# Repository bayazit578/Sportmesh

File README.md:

# Sportmesh

## Описание проекта
Cистема КП для спортивного ориентирования, трейлов с возможностью мониторинга участников соревнований в реальном времени на основе кастомной mesh-сети

## Прошивка

Прошивка использует `Arduino`-фреймворк а преимущества лежащего под ней
фреймворка `esp-idf` (например задачи, очереди и семафоры из `FreeRTOS`)

### Зависимости

| Библиотека | Версия |
| --- | --- |
| [LoRaMesher][loramesher] | `1.0.0` |
| [RadioLib][radiolib] | `7.8.1` |
| [MFRC522][mfrc522] | `1.4.12` |
| [TM16xx LEDs and Buttons][tm16xx] | `0.7.2512` |

[loramesher]: https://github.com/LoRaMesher/LoRaMesher
[radiolib]: https://github.com/jgromes/RadioLib
[mfrc522]: https://github.com/miguelbalboa/rfid
[tm16xx]: https://github.com/maxint-rd/TM16xx

### Сборка

`debug`-конфигурация:
```shell
pio run -e debug
```

`release`-конфигурация:
```shell
pio run -e release
```

### Документация

Установите Doxygen и выполните:

```shell
doxygen Doxyfile
xdg-open docs/html/index.html
```

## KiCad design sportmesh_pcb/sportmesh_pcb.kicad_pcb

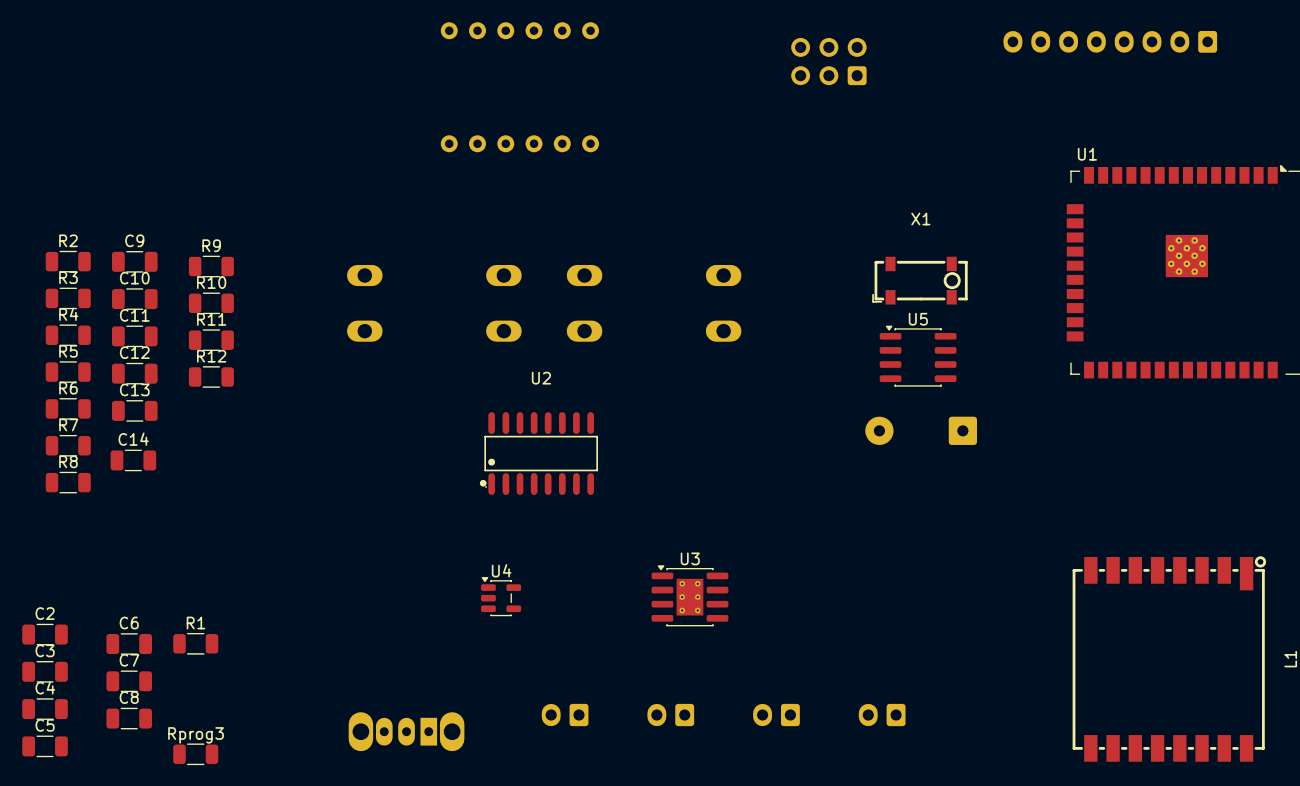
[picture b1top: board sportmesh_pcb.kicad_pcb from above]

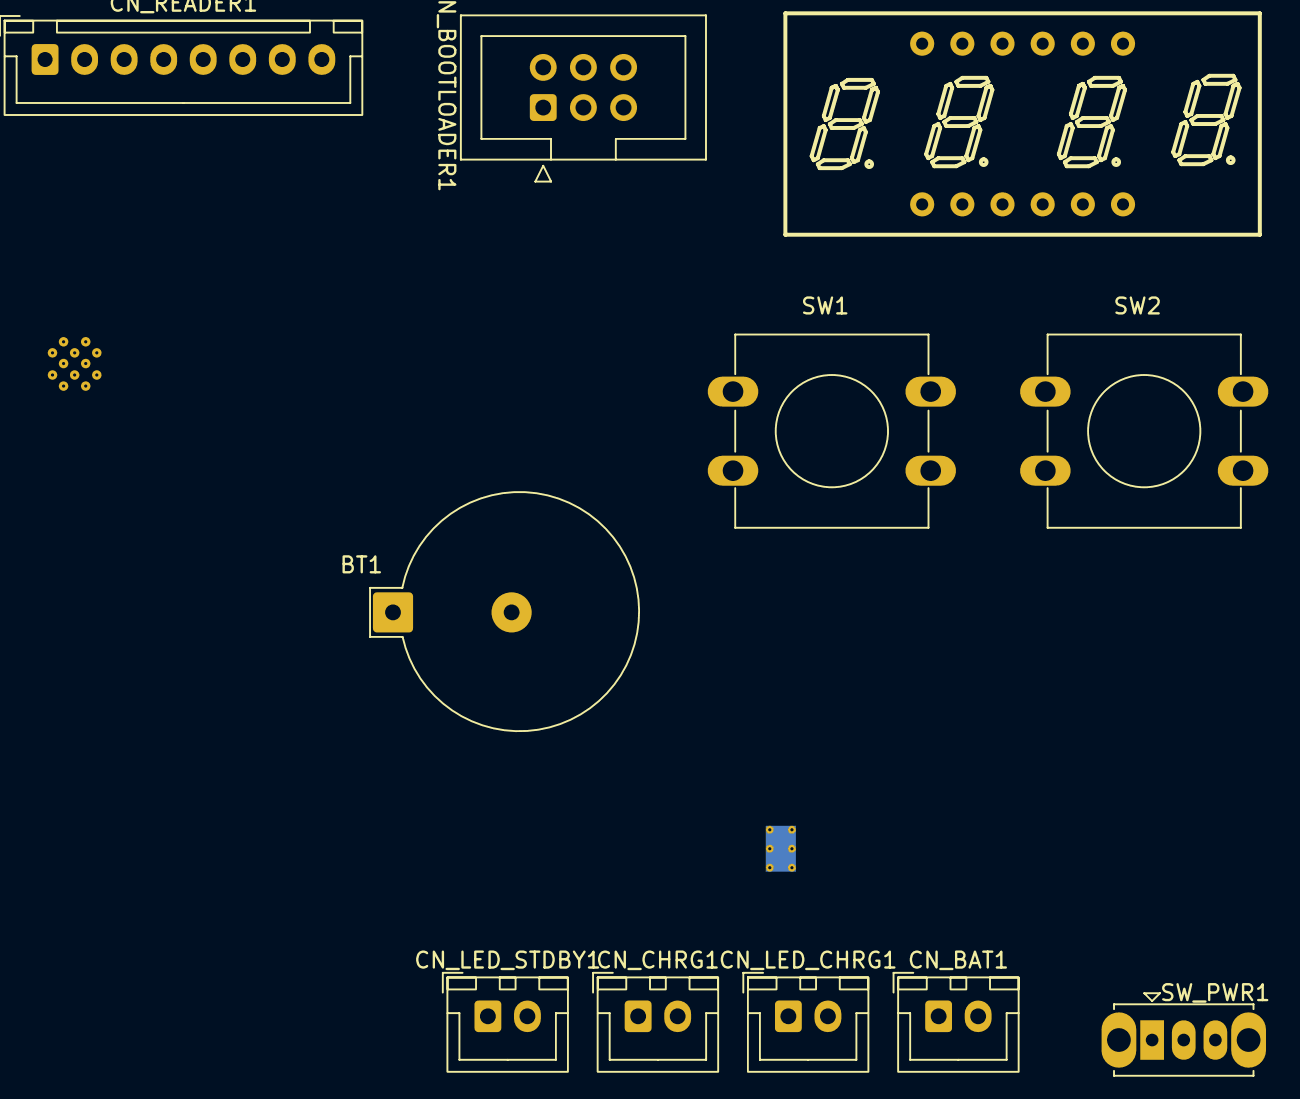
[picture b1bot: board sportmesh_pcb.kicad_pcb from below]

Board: 2 copper layers, 44 parts (11 on the bottom side), 45 nets, no tracks yet.

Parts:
BT1: Battery_Cell; BatteryHolder_KLS5-CR1220-01
C2, C4, C6: 10uF; C_1206_3216Metric
C3, C5, C10, C11: 0.1uF; C_1206_3216Metric
C7, C8, C9, C12, C13: 1uF; C_1206_3216Metric
C14: 3.3uF; C_1206_3216Metric
CN_BAT1: Conn_01x02_Pin; JST_XH_B2B-XH-A_1x02_P2.50mm_Vertical
CN_BOOTLOADER1: Conn_02x03_Odd_Even; IDC-Header_2x03_P2.54mm_Vertical
CN_CHRG1: Conn_01x02_Pin; JST_XH_B2B-XH-A_1x02_P2.50mm_Vertical
CN_LED_CHRG1: Conn_01x02_Pin; JST_XH_B2B-XH-A_1x02_P2.50mm_Vertical
CN_LED_STDBY1: Conn_01x02_Pin; JST_XH_B2B-XH-A_1x02_P2.50mm_Vertical
CN_READER1: Conn_01x08_Socket; JST_XH_B8B-XH-A_1x08_P2.50mm_Vertical
L1: RA-01SH; WIRELM-SMD_RA-01SH
LED1: FJ3461AH; LED-SEG-TH_12P-L30.0-W14.0-P2.54-S10.16-BL
R1, R12: 1K; R_1206_3216Metric
R2, R3: 3.3K; R_1206_3216Metric
R4, R5, R6, R7, R8, R9, R10, R11: 10K; R_1206_3216Metric
Rprog3: 3.3K; R_1206_3216Metric
SW1, SW2: SW_SPST; SW_PUSH-12mm
SW_PWR1: SW_SPDT; SW_Slide_SPDT_Straight_CK_OS102011MS2Q
U1: ESP32-WROOM-32D
U2: TM1650_C18211636; SOIC-16_L9.9-W3.9-P1.27-LS6.0-BL
U3: TP4056-42-ESOP8; SOIC-8-1EP_3.9x4.9mm_P1.27mm_EP2.41x3.3mm_ThermalVias
U4: TLV75733PDBV; SOT-23-5
U5: PCF8523T; SOIC-8_3.9x4.9mm_P1.27mm
X1: 6LC32768F06UC; OSC-SMD_4P-L8.0-W3.2-BL

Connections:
+3V3: C2.1, C3.1, C4.1, C5.1, C8.1, CN_BOOTLOADER1.2, CN_READER1.8, L1.3 (3.3V), R4.1, R5.1, R6.1, R7.1, R8.1, R9.1, R10.1, R11.2, R12.1, U1.2 (VDD), U2.10 (VDD), U4.5 (OUT)
/sheet_1/IO_0: CN_BOOTLOADER1.6, U1.25 (IO0)
/sheet_1/IO_5: L1.15 (NSS), U1.29 (IO5)
/sheet_1/IO_16: L1.4 (RESET), U1.27 (IO16)
/sheet_1/IO_17: L1.10 (BUSY), U1.28 (IO17)
/sheet_1/IO_18: L1.12 (SCK), U1.30 (IO18)
/sheet_1/IO_19: L1.13 (MISO), U1.31 (IO19)
/sheet_1/IO_22: L1.6 (DIO1), U1.36 (IO22)
/sheet_1/IO_23: L1.14 (MOSI), U1.37 (IO23)
/sheet_1/IO_32: R10.2, U1.8 (IO32), U5.6 (SCL)
/sheet_1/IO_33: R9.2, U1.9 (IO33), U5.5 (SDA)
/sheet_1/IO_EN: CN_BOOTLOADER1.1, R4.2, U1.3 (EN)
/sheet_1/IO_RX0: CN_BOOTLOADER1.5, U1.34 (RXD0/IO3)
/sheet_1/IO_TX0: CN_BOOTLOADER1.3, U1.35 (TXD0/IO1)
/sheet_2/IO_25: R2.2, R3.1
/sheet_2/PWR_BAT: C9.1, CN_BAT1.1, SW_PWR1.2 (B), U3.5 (BAT)
/sheet_2/PWR_BAT_IN: C7.1, R2.1, SW_PWR1.3 (C), U4.1 (IN), U4.3 (EN)
/sheet_2/PWR_CHRG: CN_CHRG1.2, U3.8 (CE)
/sheet_3/IO_21: C13.1, R8.2, SW1.2 (B)
/sheet_3/IO_32: C11.1, R5.2, U2.2 (SCL)
/sheet_3/IO_33: C10.1, R6.2, U2.3 (SDA)
/sheet_3/IO_34: C12.1, R7.2, SW2.2 (B)
/sheet_3/LED_BUS0: LED1.12 (G1), U2.1 (DIGI)
/sheet_3/LED_BUS1: LED1.9 (G2), U2.5 (DIG2)
/sheet_3/LED_BUS2: LED1.8 (G3), U2.6 (DIG3)
/sheet_3/LED_BUS3: LED1.6 (G4), U2.7 (DIG4)
/sheet_3/LED_BUS4: LED1.11 (a), U2.8 (A/K11)
/sheet_3/LED_BUS5: LED1.7 (b), U2.9 (B/K12)
/sheet_3/LED_BUS6: LED1.4 (c), U2.11 (C/K13)
/sheet_3/LED_BUS7: LED1.2 (d), U2.12 (D/K14)
/sheet_3/LED_BUS8: LED1.1 (e), U2.13 (E/K15)
/sheet_3/LED_BUS9: LED1.5 (g), U2.14 (F/K15)
/sheet_3/LED_BUS10: LED1.10 (f), U2.15 (H/K16)
/sheet_3/LED_BUS11: LED1.3 (dp), U2.16 (DP/KP)
GND: BT1.2 (-), C2.2, C3.2, C4.2, C5.2, C6.2, C7.2, C8.2, C9.2, C10.2, C11.2, C12.2, C13.2, C14.2, CN_BAT1.2, CN_BOOTLOADER1.4, CN_CHRG1.1, CN_READER1.6, L1.2 (GND), L1.9 (GND), L1.16 (GND), R3.2, Rprog3.2, SW1.1 (A), SW2.1 (A), U1.1 (GND), U1.15 (GND), U1.38 (GND), U1.39 (GND), U2.4 (GND), U3.1 (TEMP), U3.3 (GND), U4.2 (GND), U5.4 (VSS)
unnamed: BT1.1 (+), U5.3 (VBAT)
unnamed: CN_LED_CHRG1.1, CN_LED_STDBY1.1, R1.1
unnamed: CN_LED_CHRG1.2, U3.7 (~CHRG)
unnamed: CN_LED_STDBY1.2, U3.6 (~STDBY)
unnamed: Rprog3.1, U3.2 (PROG)
unnamed: C6.1, U3.4 (V_{CC})
unnamed: U5.1 (OSCI), X1.1
unnamed: U5.2 (OSCO), X1.4
unnamed: C14.1, R12.2, U5.8 (VDD)
unnamed: R11.1, U5.7 (~INT1/CLKOUT)
